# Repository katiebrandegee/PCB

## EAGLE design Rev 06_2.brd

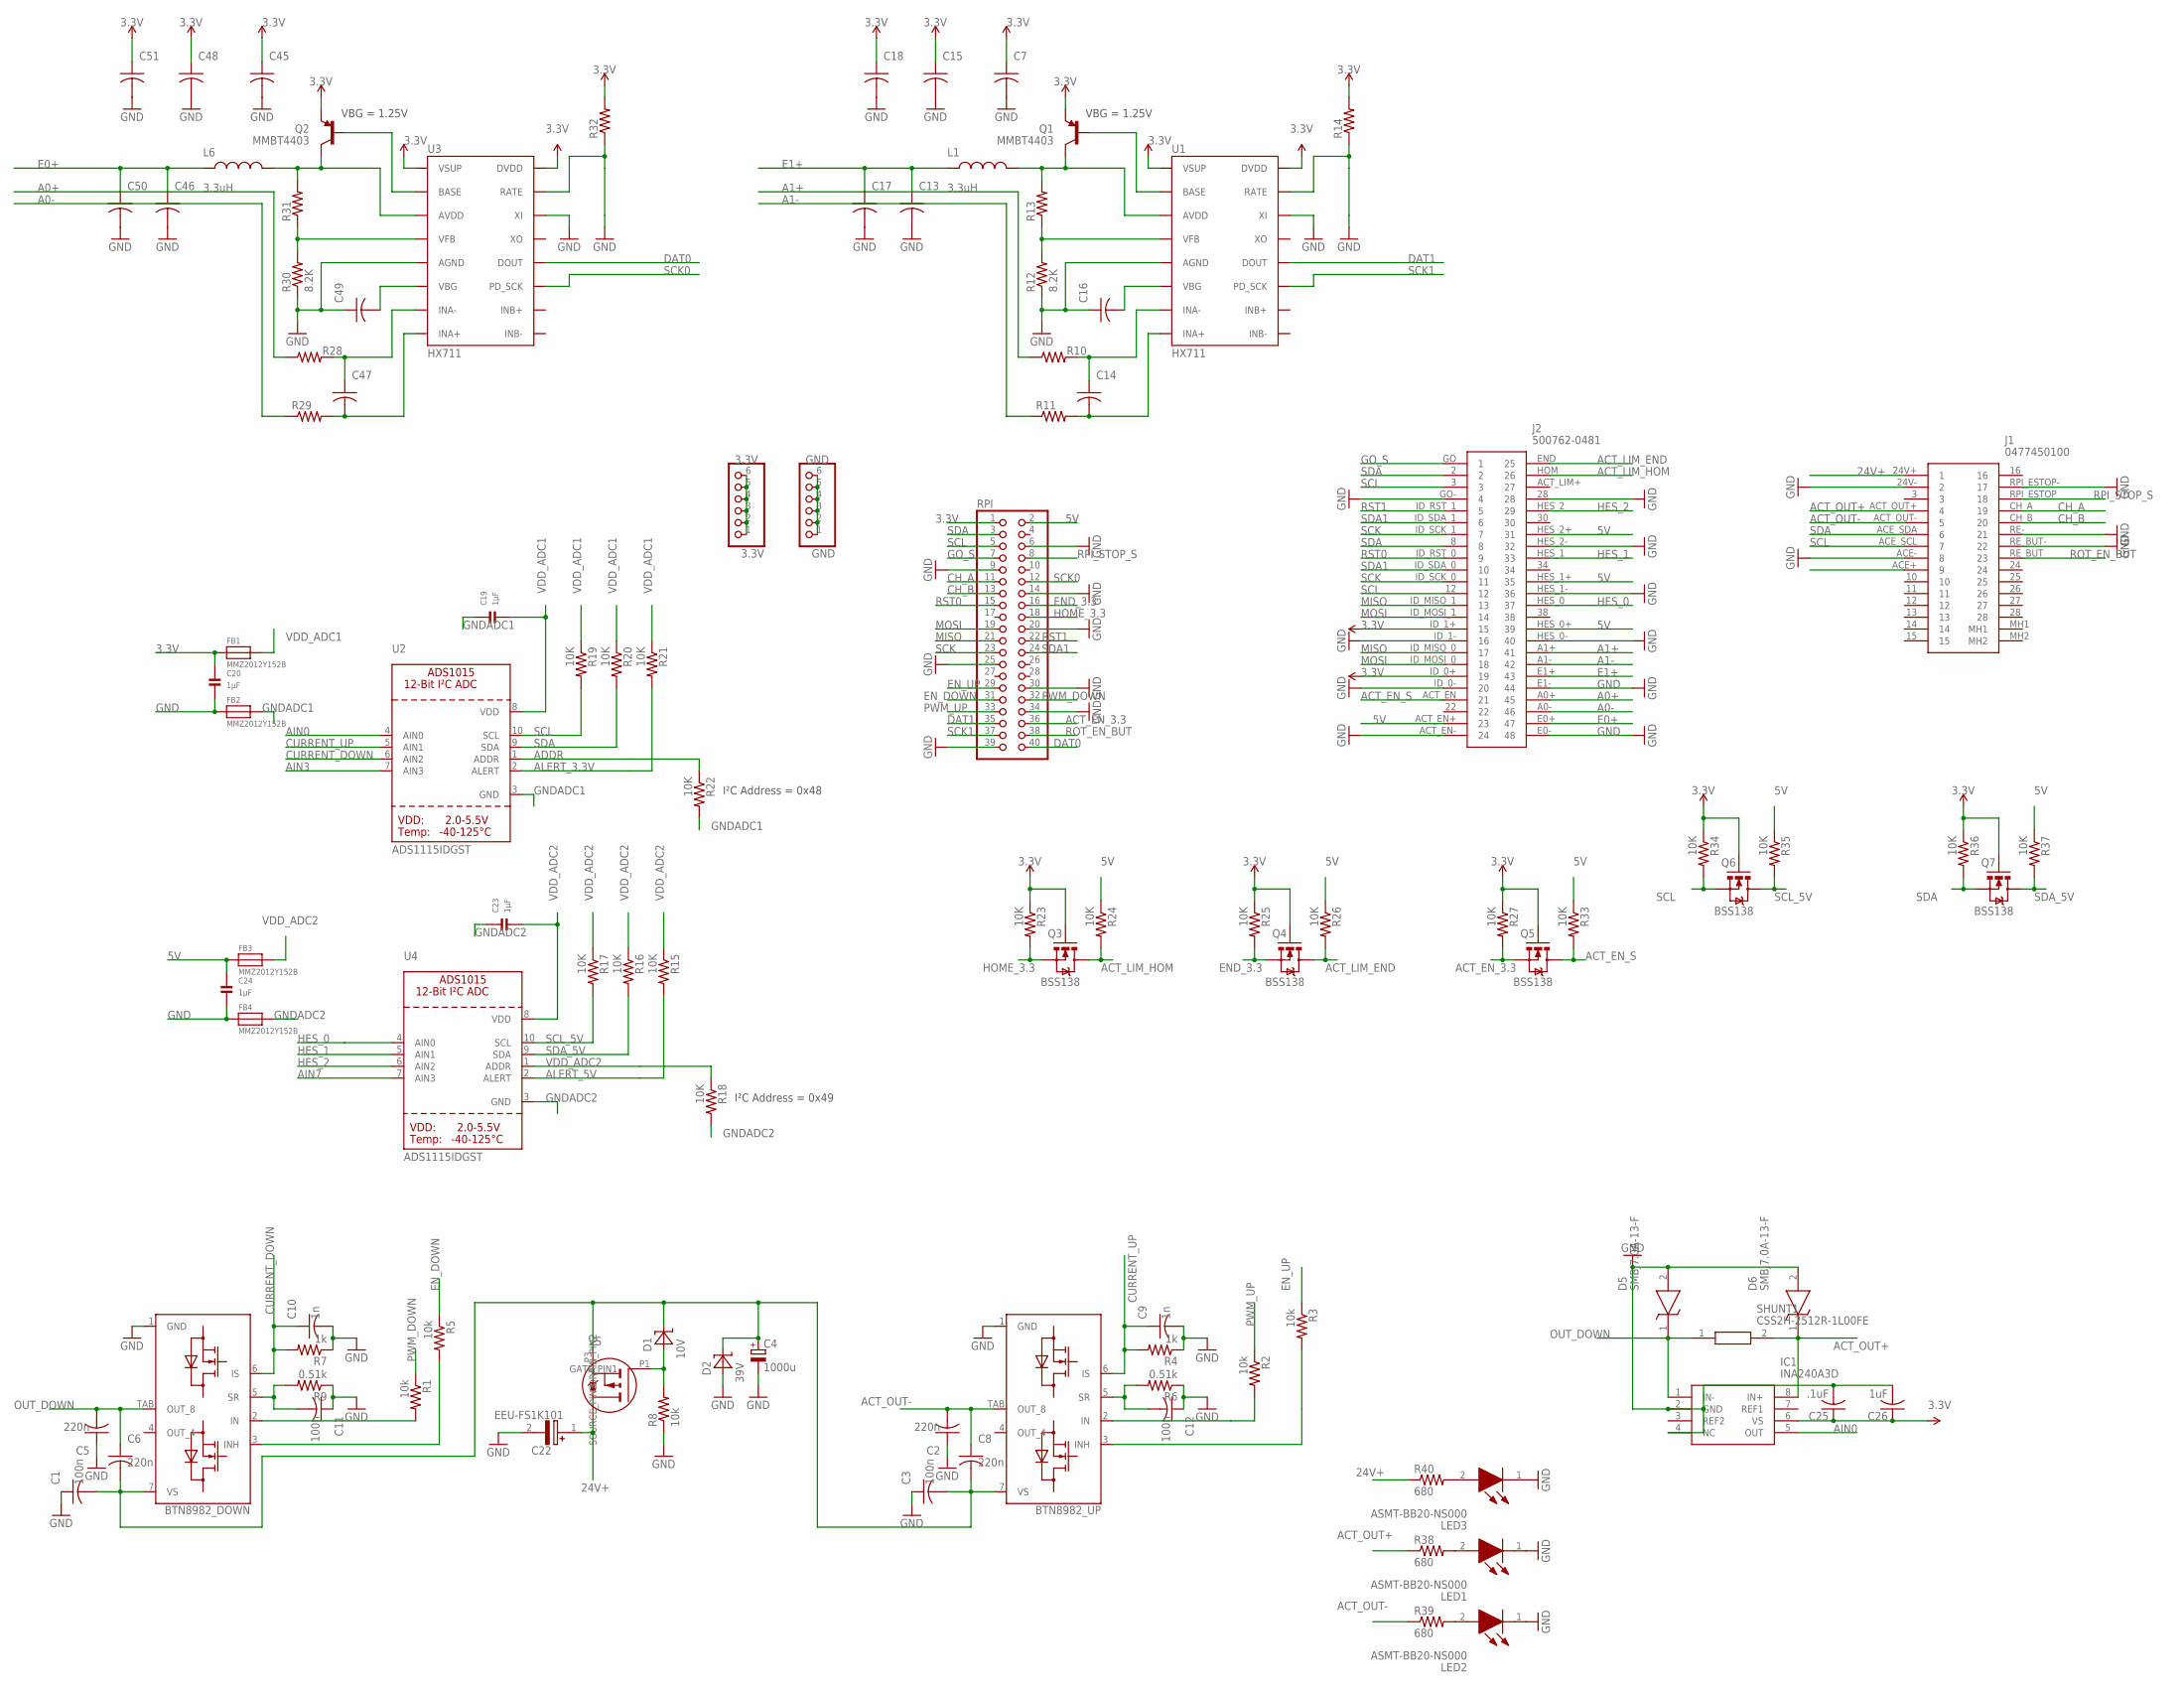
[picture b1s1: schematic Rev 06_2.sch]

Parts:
3.3V: PINHD-1X6; 1X06
BTN8982_DOWN, BTN8982_UP: HW-INFINEON_BTN8982; HW-INFINEON_TO263-7-1
C1, C3, C12: 100n; C0603K
C2, C5, C6, C8: 220n; C0603K
C4: 1000u; RCL_E5-13
C7, C13, C45, C46: 10uF; C1206K
C9, C10: 1n; C0603K
C11: 100n; C0603
C14, C15, C16, C17, C18, C47, C48, C49, C50, C51: 0.1uF; C1206K
C19, C20, C23, C24: 1µF; 1206
C22: EEU-FS1K101; CAPPRD500W65D1000H1400
C25: .1uF; C1206K
C26: 1uF; C1206K
D1: 10V; SMD-PACKAGES_SOD80
D2: 39V; SMD-PACKAGES_MELF-D
D5, D6: SMBJ7.0A-13-F; DIOM5336X250N
FB1, FB2, FB3, FB4: MMZ2012Y152B; 0805
GND: PINHD-1X6; 1X06
IC0: HW_INFINEON_IPD90P04P4L-04; HW-INFINEON_TO-252-3-313-L
IC1: INA240A3D; SOIC127P600X175-8N
J1: 0477450100
J2: 500762-0481
L1, L6: 3.3uH; 1210
LED1, LED2, LED3: ASMT-BB20-NS000; LEDM3224X250N
Q1, Q2: MMBT4403; SOT23-3
Q3, Q4, Q5, Q6, Q7: BSS138; SOT23-3
R1, R2, R3, R5, R8: 10k; 0603-RES
R4, R7: 1k; 0603-RES
R6, R9: 0.51k; 0603-RES
R10, R11, R28, R29: 100; R2010
R12, R30: 8.2K; R2010
R13, R31: 20k; R2010
R14, R15, R16, R17, R18, R19, R20, R21, R22, R23, R24, R25, R26, R27, R32, R33, R34, R35, R36, R37: 10K; R2010
R38, R39, R40: 680; 1206
RPI: PINHD-2X20; 2X20
SHUNT1: CSS2H-2512R-1L00FE; CSS2H2512R1L00FE
U1, U3: HX711; SO16
U2, U4: ADS1115IDGST; MSOP10

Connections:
3.3V: 3.3V.1, 3.3V.2, 3.3V.3, 3.3V.4, 3.3V.5, 3.3V.6, C7.1, C15.1, C18.1, C20.1, C25.1, C26.1, C45.1, C48.1, C51.1, FB1.1, IC1.6 (VS), J2.ID_0+ (19), J2.ID_1+ (15), Q1.2 (E), Q2.2 (E), Q3.1 (G), Q4.1 (G), Q5.1 (G), Q6.1 (G), Q7.1 (G), R14.2, R23.1, R25.1, R27.1, R32.2, R34.1, R36.1, RPI.1 (3.3V0), U1.1 (VSUP), U1.16 (DVDD), U3.1 (VSUP), U3.16 (DVDD)
5V: C24.1, FB3.1, J2.ACT_EN+ (23), J2.HES_0+ (39), J2.HES_1+ (35), J2.HES_2+ (31), R24.1, R26.1, R33.1, R35.1, R37.1, RPI.2 (5V0)
24V+: C22.1 (+), IC0.P2 (DRAIN_PIN2), J1.24V+ (1), R40.1
A0+: J2.A0+ (45), R28.1
A0-: J2.A0- (46), R29.1
A1+: J2.A1+ (41), R10.1
A1-: J2.A1- (42), R11.1
ACT_EN_3.3: Q5.2 (S), R27.2, RPI.36 (16)
ACT_EN_S: J2.ACT_EN (21), Q5.3 (D), R33.2
ACT_LIM_END: J2.END (25), Q4.3 (D), R26.2
ACT_LIM_HOM: J2.HOM (26), Q3.3 (D), R24.2
ACT_OUT+: D6.1 (K), IC1.8 (IN+), J1.ACT_OUT+ (4), R38.1, SHUNT1.2
ACT_OUT-: BTN8982_UP.TAB (OUT_8), C2.2, C8.1, J1.ACT_OUT- (5), R39.1
ADDR: R22.1, U2.1 (ADDR)
AIN0: IC1.5 (OUT), U2.4 (AIN0)
AIN3: U2.7 (AIN3)
AIN7: U4.7 (AIN3)
ALERT_3.3V: R21.2, U2.2 (ALERT)
ALERT_5V: R15.2, U4.2 (ALERT)
CH_A: J1.CH_A (19), RPI.11 (17)
CH_B: J1.CH_B (20), RPI.13 (27)
CURRENT_DOWN: BTN8982_DOWN.6 (IS), C10.1, R7.2, U2.6 (AIN2)
CURRENT_UP: BTN8982_UP.6 (IS), C9.1, R4.2, U2.5 (AIN1)
DAT0: RPI.40 (21), U3.12 (DOUT)
DAT1: RPI.35 (19), U1.12 (DOUT)
E0+: C46.1, C50.1, J2.E0+ (47), L6.1
E1+: C13.1, C17.1, J2.E1+ (43), L1.1
END_3.3: Q4.2 (S), R25.2, RPI.16 (23)
EN_DOWN: R5.1, RPI.31 (6)
EN_UP: R3.1, RPI.29 (5)
GND: BTN8982_DOWN.1 (GND), BTN8982_UP.1 (GND), C1.1, C2.1, C3.1, C4.-, C5.1, C7.2, C9.2, C10.2, C11.1, C12.1, C13.2, C15.2, C16.1, C17.2, C18.2, C20.2, C22.2 (-), C24.2, C25.2, C26.2, C45.2, C46.2, C48.2, C49.1, C50.2, C51.2, D2.A, D5.2 (A), D6.2 (A), FB2.1, FB4.1, GND.1, GND.2, GND.3, GND.4, GND.5, GND.6, IC1.2 (GND), IC1.4 (NC), J1.24V- (2), J1.ACE- (8), J1.RE- (21), J1.RE_BUT- (22), J1.RPI_ESTOP- (17), J2.28, J2.ACT_EN- (24), J2.E0- (48), J2.E1- (44), J2.GO- (4), J2.HES_0- (40), J2.HES_1- (36), J2.HES_2- (32), J2.ID_0- (20), J2.ID_1- (16), LED1.1 (K), LED2.1 (K), LED3.1 (K), R4.1, R6.1, R7.1, R8.1, R9.1, R12.1, R14.1, R30.1, R32.1, RPI.6 (GND4), RPI.9 (GND0), RPI.14 (GND5), RPI.20 (GND6), RPI.25 (GND1), RPI.30 (GND7), RPI.34 (GND8), RPI.39 (GND3), U1.5 (AGND), U1.14 (XI), U1.15 (RATE), U3.5 (AGND), U3.14 (XI), U3.15 (RATE)
GNDADC1: C19.1, FB2.2, R22.2, U2.3 (GND)
GNDADC2: C23.1, FB4.2, R18.2, U4.3 (GND)
GO_S: J2.GO (1), RPI.7 (4)
HES_0: J2.HES_0 (37), U4.4 (AIN0)
HES_1: J2.HES_1 (33), U4.5 (AIN1)
HES_2: J2.HES_2 (29), U4.6 (AIN2)
HOME_3.3: Q3.2 (S), R23.2, RPI.18 (24)
IN2: BTN8982_UP.2 (IN), R2.2
INH1: BTN8982_DOWN.3 (INH), R5.2
INH2: BTN8982_UP.3 (INH), R3.2
MISO: J2.ID_MISO_0 (17), J2.ID_MISO_1 (13), RPI.21 (9)
MOSI: J2.ID_MOSI_0 (18), J2.ID_MOSI_1 (14), RPI.19 (10)
unnamed: BTN8982_DOWN.2 (IN), R1.2
unnamed: Q1.1 (B), U1.2 (BASE)
unnamed: R12.2, R13.1, U1.4 (VFB)
unnamed: C16.2, U1.6 (VBG)
unnamed: L1.2, Q1.3 (C), R13.2, U1.3 (AVDD)
unnamed: C14.1, R10.2, U1.7 (INA-)
unnamed: C14.2, R11.2, U1.8 (INA+)
unnamed: LED1.2 (A), R38.2
unnamed: D1.A, IC0.P1 (GATE_PIN1), R8.2
unnamed: LED2.2 (A), R39.2
unnamed: LED3.2 (A), R40.2
unnamed: Q2.1 (B), U3.2 (BASE)
unnamed: R30.2, R31.1, U3.4 (VFB)
unnamed: C49.2, U3.6 (VBG)
unnamed: L6.2, Q2.3 (C), R31.2, U3.3 (AVDD)
unnamed: C47.1, R28.2, U3.7 (INA-)
unnamed: C47.2, R29.2, U3.8 (INA+)
OUT_DOWN: BTN8982_DOWN.TAB (OUT_8), C5.2, C6.1, D5.1 (K), IC1.1 (IN-), SHUNT1.1
PWM_DOWN: R1.1, RPI.32 (12)
PWM_UP: R2.1, RPI.33 (13)
ROT_EN_BUT: J1.RE_BUT (23), RPI.38 (20)
RPI_STOP_S: J1.RPI_ESTOP (18), RPI.8 (14)
RST0: J2.ID_RST_0 (9), RPI.15 (22)
RST1: J2.ID_RST_1 (5), RPI.22 (25)
SCK: J2.ID_SCK_0 (11), J2.ID_SCK_1 (7), RPI.23 (11)
SCK0: RPI.12 (18), U3.11 (PD_SCK)
SCK1: RPI.37 (26), U1.11 (PD_SCK)
SCL: J1.ACE_SCL (7), J2.3, J2.12, Q6.2 (S), R19.2, R34.2, RPI.5 (3), U2.10 (SCL)
SCL_5V: Q6.3 (D), R17.2, R35.2, U4.10 (SCL)
SDA: J1.ACE_SDA (6), J2.2, J2.8, Q7.2 (S), R20.2, R36.2, RPI.3 (2), U2.9 (SDA)
SDA1: J2.ID_SDA_0 (10), J2.ID_SDA_1 (6), RPI.24 (8)
SDA_5V: Q7.3 (D), R16.2, R37.2, U4.9 (SDA)
SR1: BTN8982_DOWN.5 (SR), C11.2, R9.2
SR2: BTN8982_UP.5 (SR), C12.2, R6.2
VDD_ADC1: C19.2, FB1.2, R19.1, R20.1, R21.1, U2.8 (VDD)
VDD_ADC2: C23.2, FB3.2, R15.1, R16.1, R17.1, R18.1, U4.1 (ADDR), U4.8 (VDD)
VS: BTN8982_DOWN.7 (VS), BTN8982_UP.7 (VS), C1.2, C3.2, C4.+, C6.2, C8.2, D1.K (C), D2.K (C), IC0.P3 (SOURCE_PIN3)

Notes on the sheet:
VBG = 1.25V
I²C Address = 0x48
I²C Address = 0x49

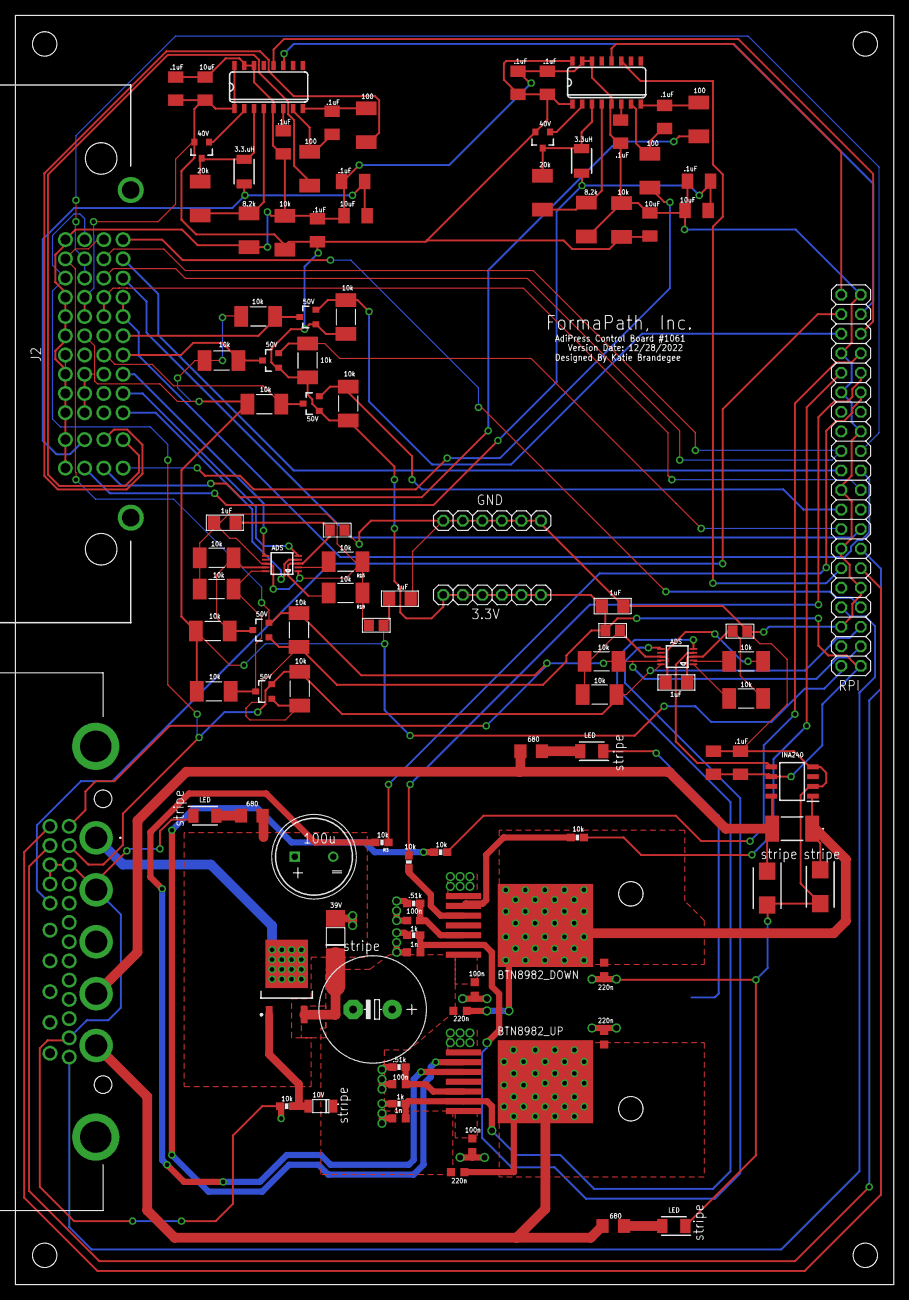
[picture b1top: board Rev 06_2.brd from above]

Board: 2 copper layers, 114.2 x 165.0 mm, 106 parts (0 on the bottom side), 78 nets.

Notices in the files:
parts and their libraries:
SparkFun-DiscreteSemi: Licensing: Creative Commons ShareAlike 4.0 International - https://creativecommons.org/licenses/by-sa/4.0
SparkFun-Aesthetics: Licensing: CC v3.0 Share-Alike You are welcome to use this library for commercial purposes.
